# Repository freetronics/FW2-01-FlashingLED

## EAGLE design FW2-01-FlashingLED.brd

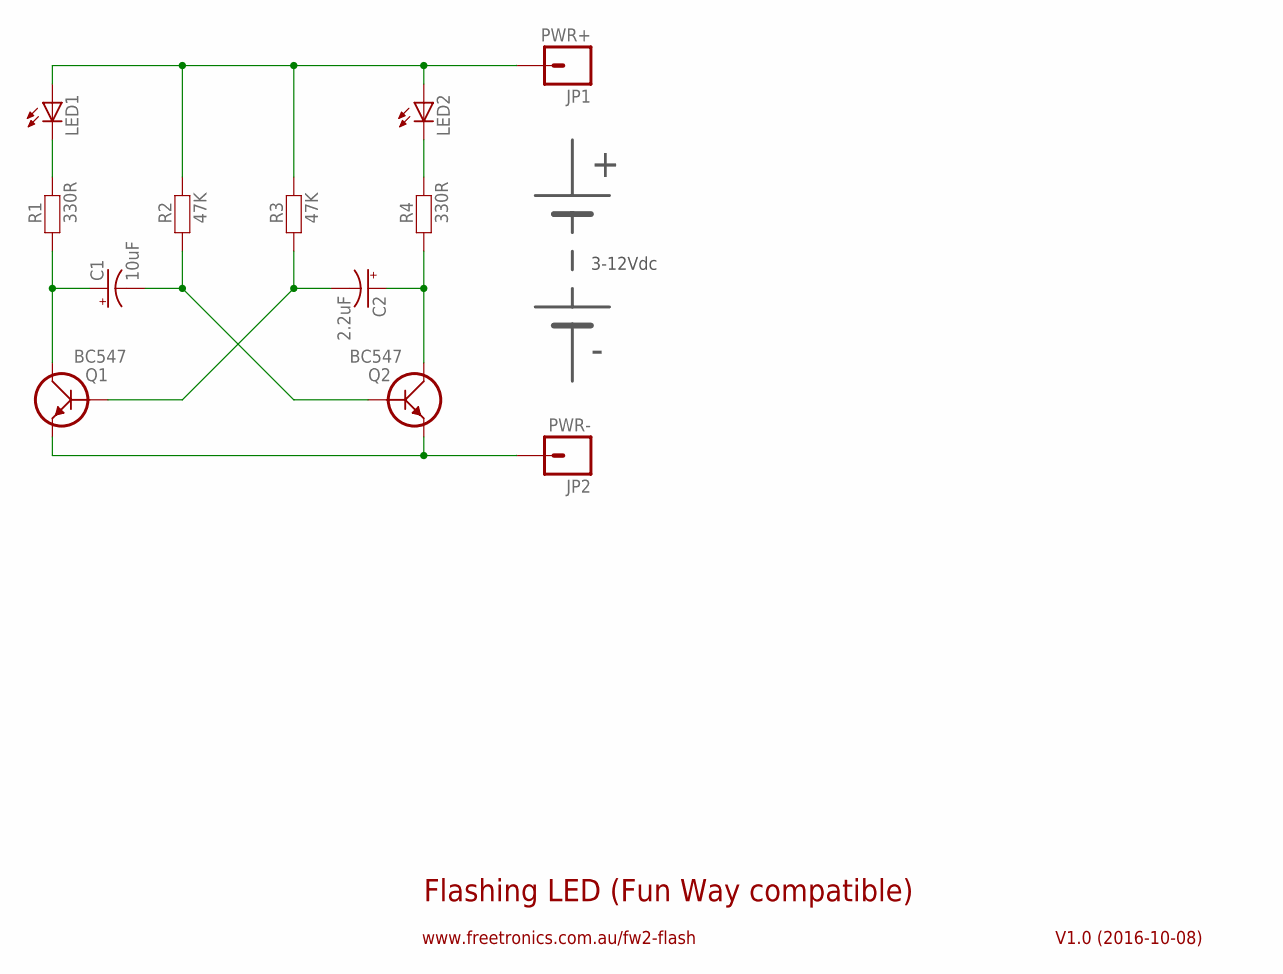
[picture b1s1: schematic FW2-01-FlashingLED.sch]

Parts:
C1: 10uF; E5-5
C2: 2.2uF; E5-5
JP1: PWR+; 1X01
JP2: PWR-; 1X01
LED1, LED2: LED5MM
Q1, Q2: BC547; TO-92
R1, R4: 330R; FREETRONICS_AXIAL-0.4
R2, R3: 47K; FREETRONICS_AXIAL-0.4

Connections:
unnamed: LED1.K (C), R1.P$2 (2)
unnamed: JP1.1, LED1.A, LED2.A, R2.P$2 (2), R3.P$2 (2)
unnamed: C1.+, Q1.1 (C), R1.P$1 (1)
unnamed: C2.+, Q2.1 (C), R4.P$1 (1)
unnamed: LED2.K (C), R4.P$2 (2)
unnamed: C2.-, Q1.2 (B), R3.P$1 (1)
unnamed: C1.-, Q2.2 (B), R2.P$1 (1)
unnamed: JP2.1, Q1.3 (E), Q2.3 (E)

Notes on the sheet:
Flashing LED (Fun Way compatible)
V1.0 (2016-10-08)
www.freetronics.com.au/fw2-flash
3-12Vdc

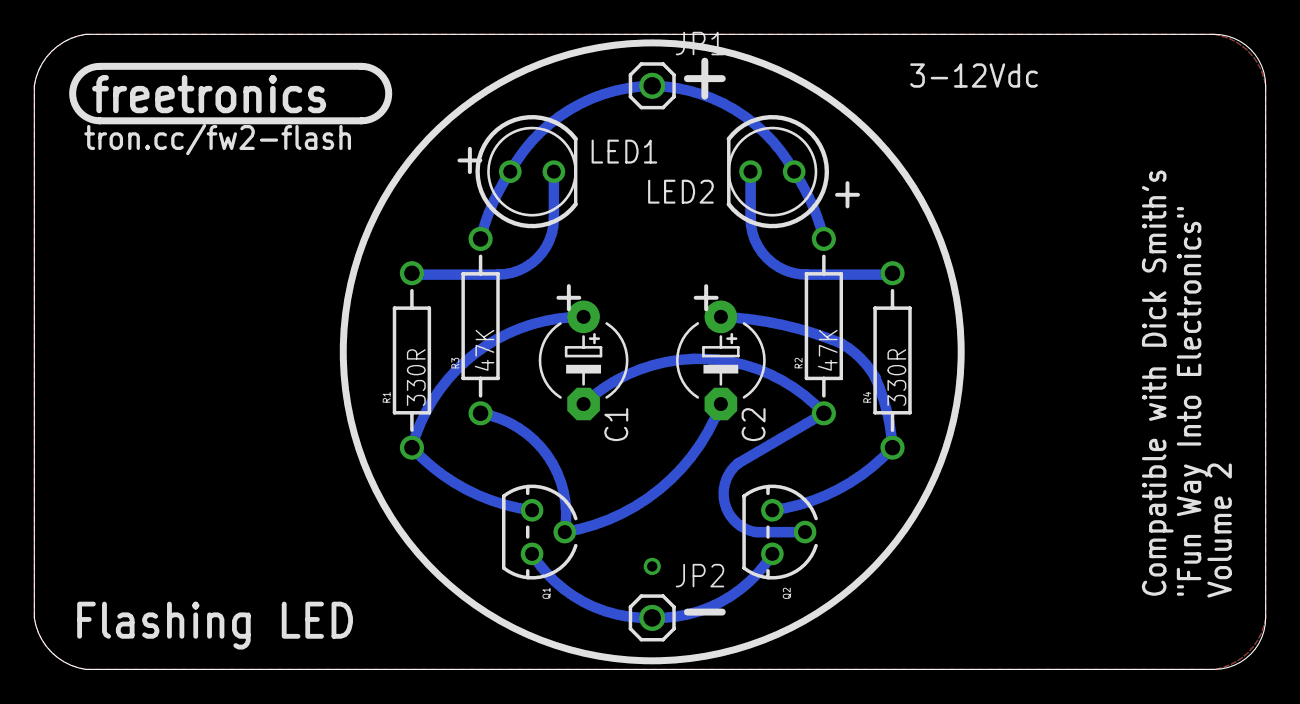
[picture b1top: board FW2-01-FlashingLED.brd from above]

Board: 2 copper layers, 71.7 x 37.0 mm, 12 parts (0 on the bottom side), 8 nets.

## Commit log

2016-10-08 Initial project import
2016-10-08 Basic board layout. Maybe almost done, needs a review
2016-10-09 Updated silkscreen and labels
2016-10-10 Increased pad size and track width

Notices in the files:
FW2-01-FlashingLED.brd:
(c) 2016 Freetronics Pty Ltd
Licensed under the TAPR
Open Hardware License
